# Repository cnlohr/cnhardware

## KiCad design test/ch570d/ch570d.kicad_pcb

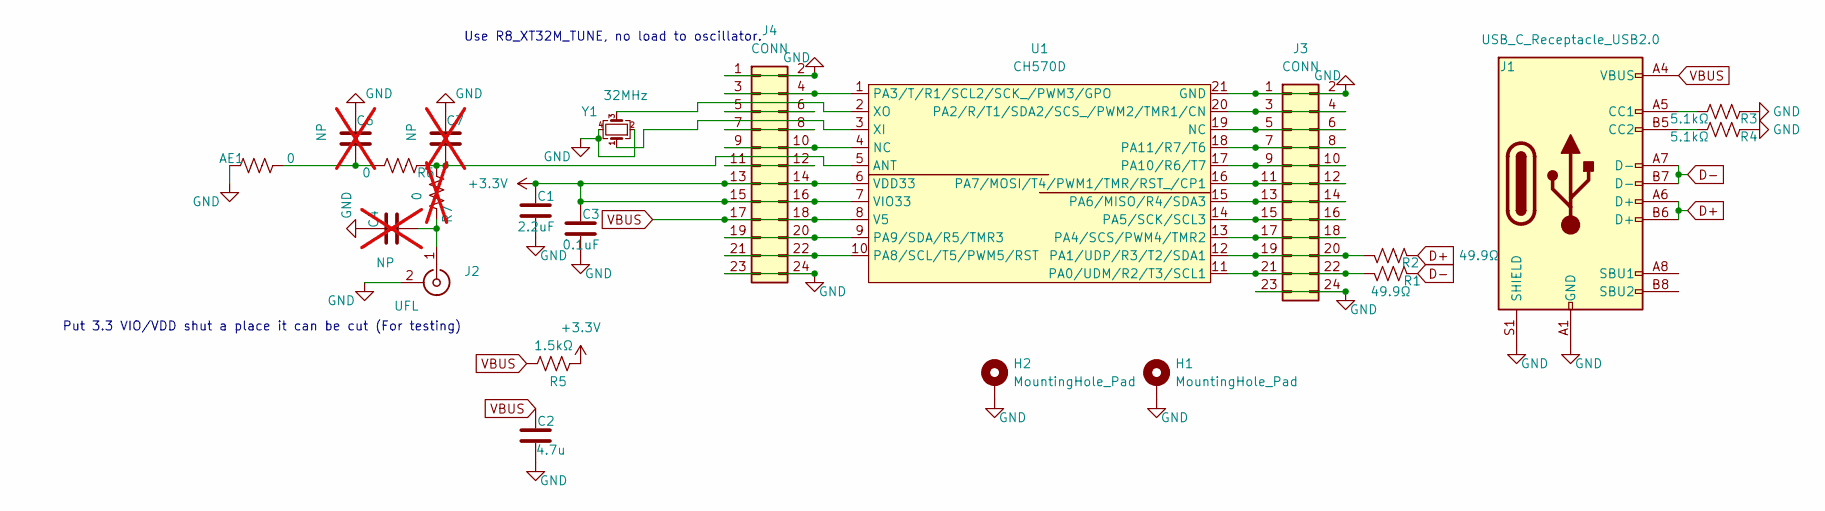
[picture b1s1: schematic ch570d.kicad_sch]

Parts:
AE1: 0; Texas_SWRA117D_2.4GHz_Right
C1: 2.2uF; C_0402_1005Metric; LCSC C12530
C2: 4.7u; C_0402_1005Metric; LCSC C23733
C3: 0.1uF; C_0402_1005Metric; LCSC C307331
C4, C6, C7: NP; C_0402_1005Metric; not fitted
H1, H2: MountingHole_Pad; MountingHole_2.2mm_M2_DIN965_Pad
J1: USB_C_Receptacle_USB2.0; USB_C_Receptacle_HRO_TYPE-C-31-M-12; LCSC C2765186
J2: UFL; U.FL_Molex_MCRF_73412-0110_Vertical; LCSC C496552
J3, J4: CONN; PinHeader_2x12_P2.54mm_Vertical; LCSC C5383110
R1, R2: 49.9Ω; R_0402_1005Metric; LCSC C25120
R3, R4: 5.1kΩ; R_0402_1005Metric; LCSC C25905
R5: 1.5kΩ; R_0402_1005Metric; LCSC C25867
R6: 0; R_0402_1005Metric; LCSC C17168
R7: 0; R_0402_1005Metric; LCSC C17168; not fitted
U1: CH570D; QFN-20-1EP_3x3mm_P0.4mm_EP1.65x1.65mm
Y1: 32MHz; Crystal_SMD_2016-4Pin_2.0x1.6mm; LCSC C2965582

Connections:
+3.3V: C1.1, C3.1, J4.13, J4.14, J4.15, J4.16, R5.2, U1.6 (VDD33), U1.7 (VIO33)
D+: J1.A6 (D+), J1.B6 (D+), R2.2
D-: J1.A7 (D-), J1.B7 (D-), R1.2
GND: AE1.2, C1.2, C2.2, C3.2, C4.1, C6.1, C7.1, H1.1, H2.1, J1.A1 (GND), J1.A12 (GND), J1.B1 (GND), J1.B12 (GND), J1.S1 (SHIELD), J2.2 (Ext), J3.1, J3.2, J3.23, J3.24, J4.1, J4.2, J4.23, J4.24, R3.2, R4.2, U1.21 (GND), Y1.2, Y1.4
unnamed: AE1.1, C6.2, R6.1
unnamed: J1.A5 (CC1), R3.1
unnamed: J1.B5 (CC2), R4.1
unnamed: C4.2, J2.1 (In), R7.1
unnamed: J3.3, J3.4, U1.20 (PA2/R/T1/SDA2/SCS_/PWM2/TMR1/CN)
unnamed: J3.5, J3.6, U1.19 (NC)
unnamed: J3.7, J3.8, U1.18 (PA11/R7/T6)
unnamed: J3.9, J3.10, U1.17 (PA10/R6/T7)
unnamed: J3.11, J3.12, U1.16 (PA7/MOSI/T4/PWM1/TMR/RST_/CP1)
unnamed: J3.13, J3.14, U1.15 (PA6/MISO/R4/SDA3)
unnamed: J3.15, J3.16, U1.14 (PA5/SCK/SCL3)
unnamed: J3.17, J3.18, U1.13 (PA4/SCS/PWM4/TMR2)
unnamed: J3.19, J3.20, R2.1, U1.12 (PA1/UDP/R3/T2/SDA1)
unnamed: J3.21, J3.22, R1.1, U1.11 (PA0/UDM/R2/T3/SCL1)
unnamed: J4.3, J4.4, U1.1 (PA3/T/R1/SCL2/SCK_/PWM3/GPO)
unnamed: J4.5, J4.6
unnamed: J4.7, J4.8
unnamed: J4.9, J4.10, U1.4 (NC)
unnamed: J4.11, J4.12
unnamed: J4.19, J4.20, U1.9 (PA9/SDA/R5/TMR3)
unnamed: J4.21, J4.22, U1.10 (PA8/SCL/T5/PWM5/RST)
unnamed: C7.2, R6.2, R7.2, U1.5 (ANT)
unnamed: U1.3 (XI), Y1.1
unnamed: U1.2 (XO), Y1.3
VBUS: C2.1, J1.A4 (VBUS), J1.A9 (VBUS), J1.B4 (VBUS), J1.B9 (VBUS), J4.17, J4.18, R5.1, U1.8 (V5)

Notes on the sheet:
Use R8_XT32M_TUNE, no load to oscillator.
Put 3.3 VIO/VDD shut a place it can be cut (For testing)

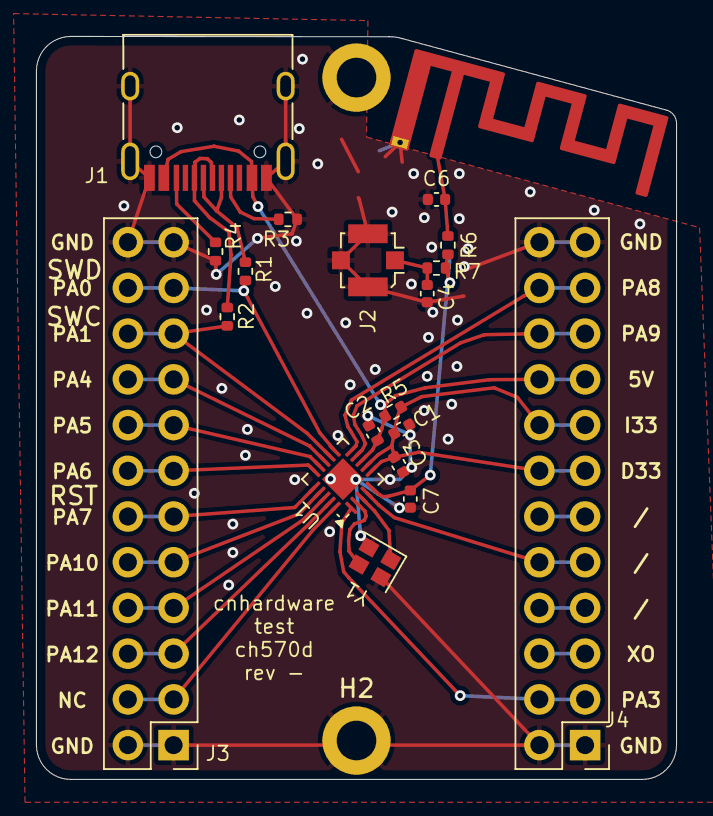
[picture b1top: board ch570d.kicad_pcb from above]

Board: 2 copper layers, 35.6 x 41.3 mm, 22 parts (0 on the bottom side), 29 nets.

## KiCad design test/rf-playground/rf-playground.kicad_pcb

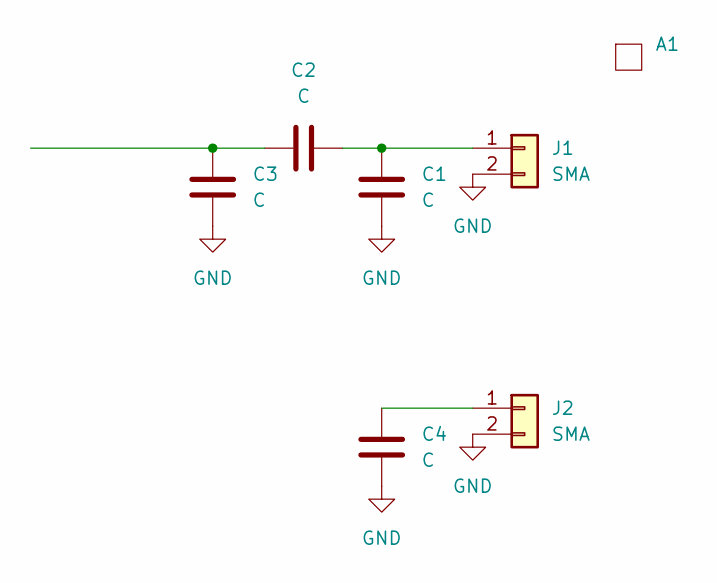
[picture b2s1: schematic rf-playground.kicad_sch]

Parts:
A1: maskgrid
C1, C2, C3, C4: C; C_0603_1608Metric
J1, J2: SMA; SMA_Amphenol_132289_EdgeMount

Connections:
GND: C1.2, C3.2, C4.2, J1.2, J2.2
unnamed: C2.1, C3.1
unnamed: C1.1, C2.2, J1.1
unnamed: C4.1, J2.1

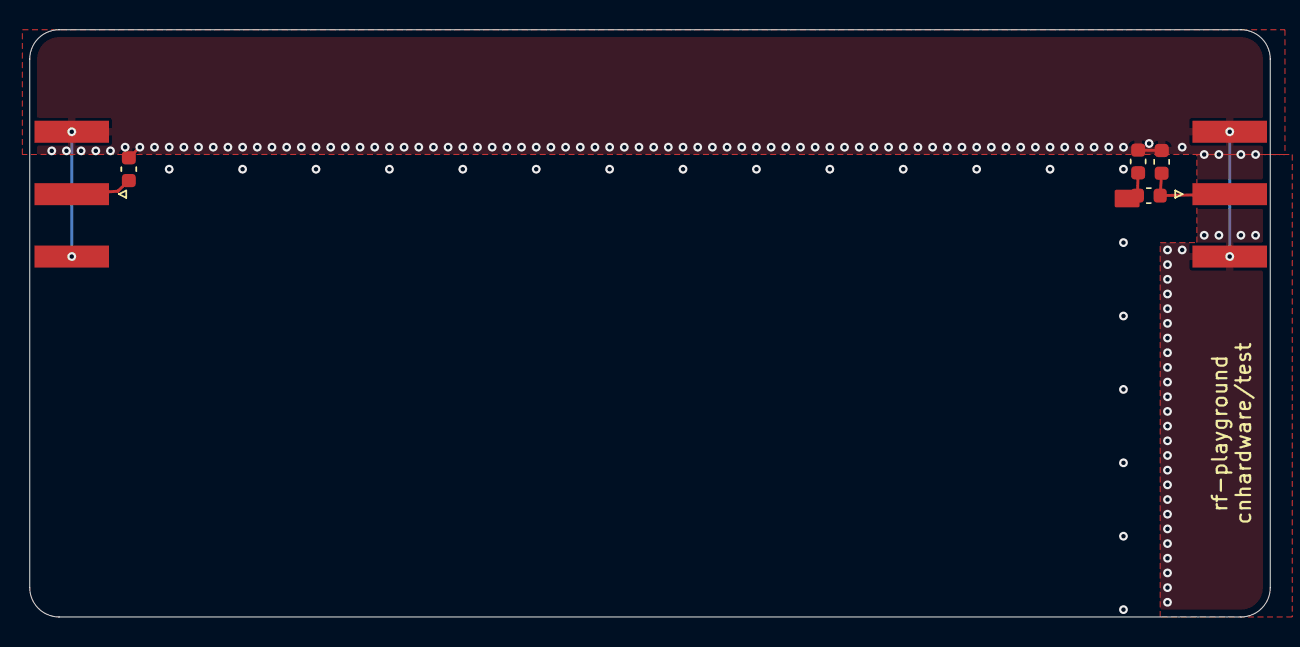
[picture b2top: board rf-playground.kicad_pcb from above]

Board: 2 copper layers, 84.5 x 40.0 mm, 8 parts (1 on the bottom side), 4 nets.

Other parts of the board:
A1#2: maskgrid

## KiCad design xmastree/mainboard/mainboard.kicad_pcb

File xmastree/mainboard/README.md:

Moved here: https://github.com/cnlohr/x32-ws2812-usbhs-breakout

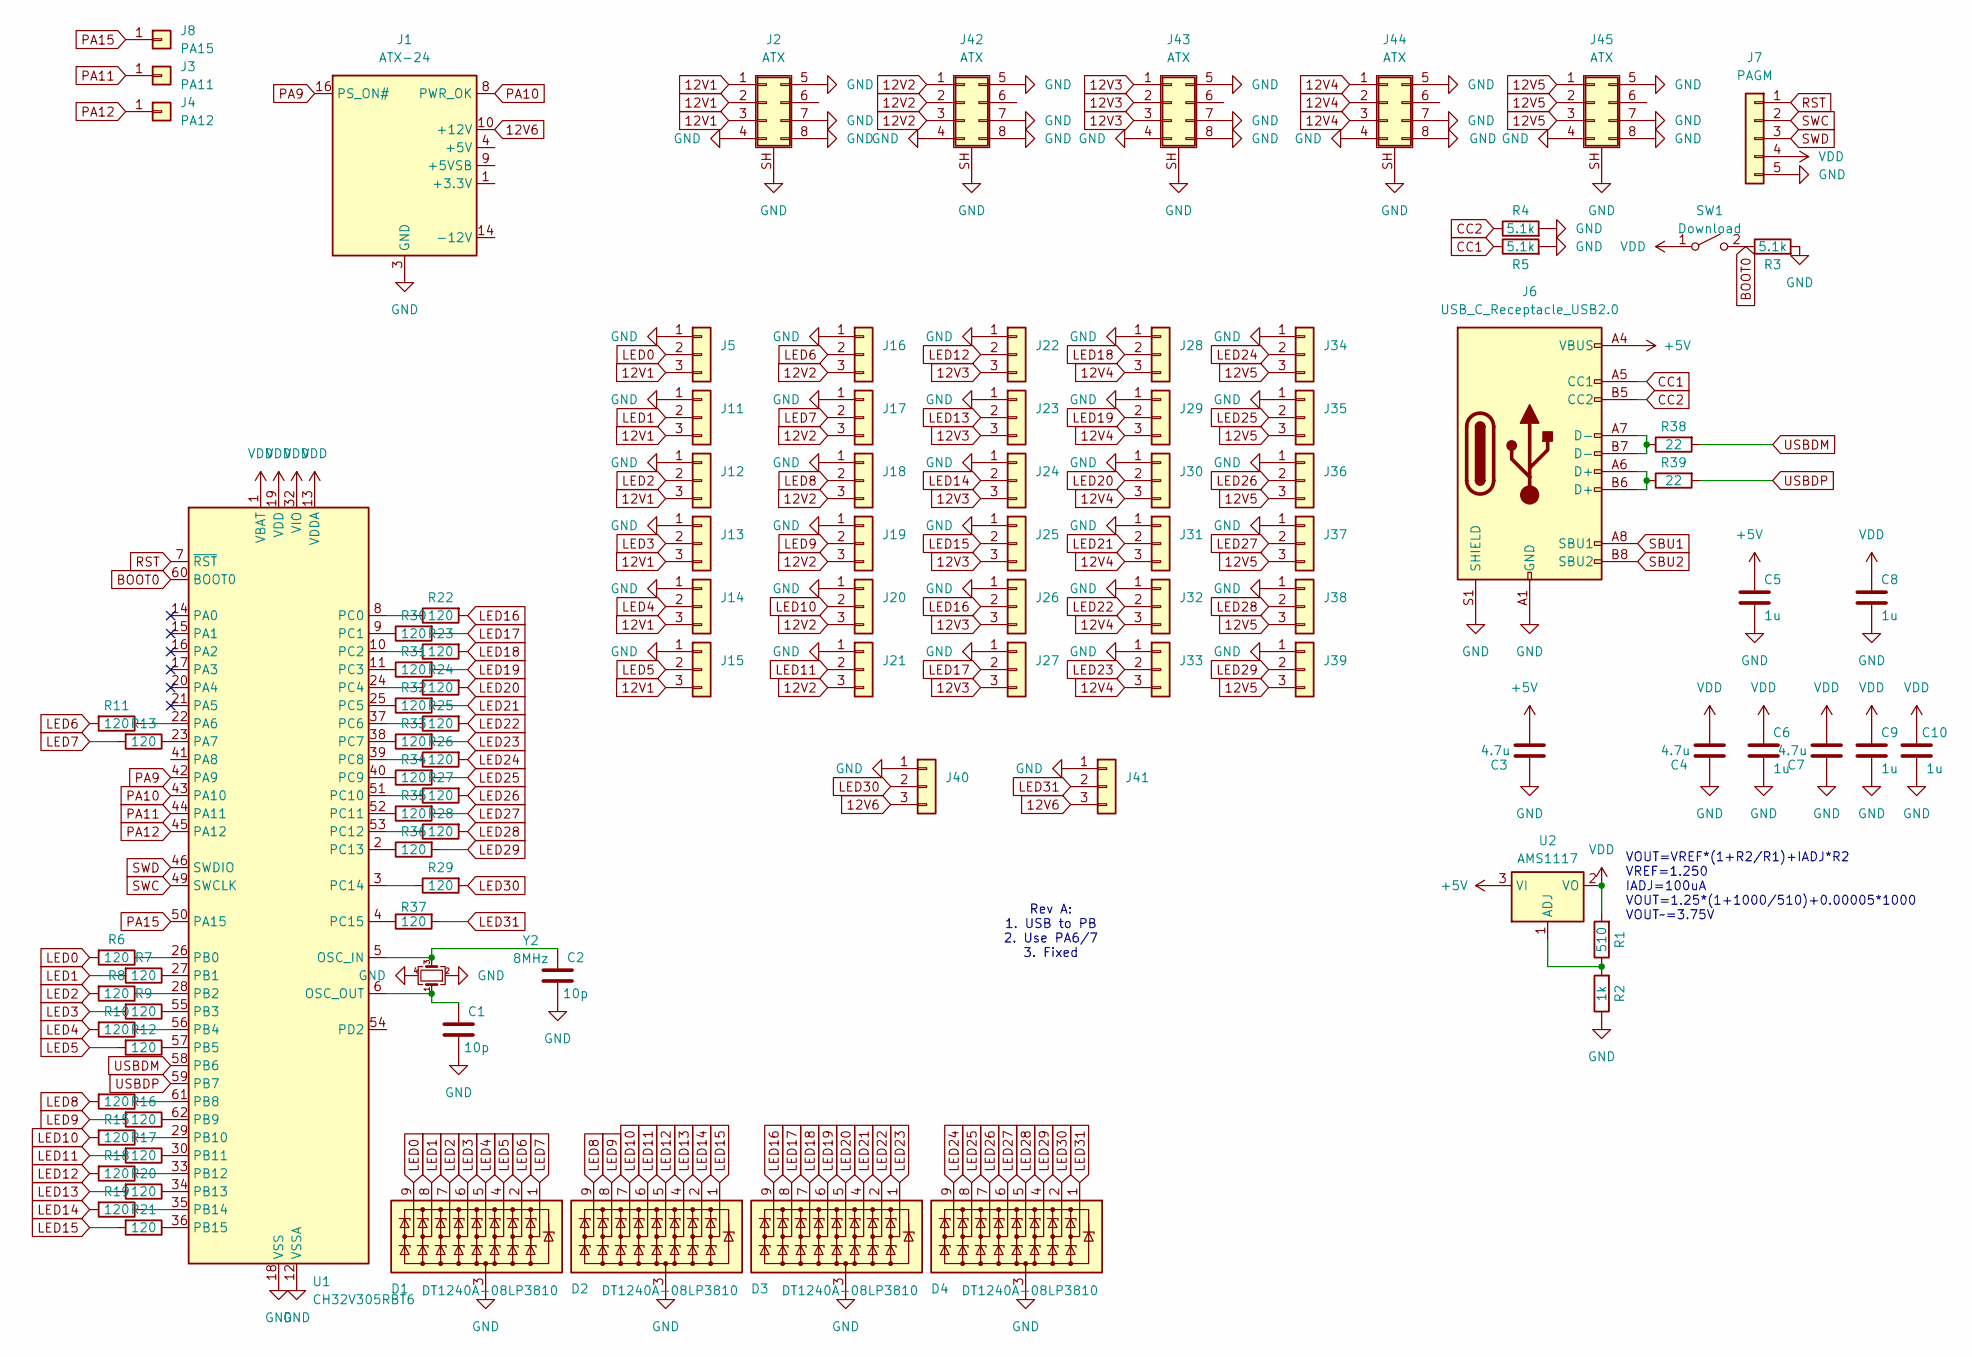
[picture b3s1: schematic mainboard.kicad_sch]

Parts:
C1, C2: 10p; R_0402_1005Metric; LCSC C32949
C3, C4, C7: 4.7u; C_0805_2012Metric; LCSC C1779
C5, C6, C8, C9, C10: 1u; R_0402_1005Metric; LCSC C52923
D1, D2, D3, D4: DT1240A-08LP3810; UDFN-9_1.0x3.8mm_P0.5mm; LCSC C526598
J1: ATX-24; Molex_Mini-Fit_Jr_5566-24A2_2x12_P4.20mm_Vertical; LCSC C114125
J2, J42, J43, J44, J45: ATX; Molex_Mini-Fit_-PCI_EXPRESS-_2x04_P4.20mm_Vertical; LCSC C2886679
J3: PA11; TestPoint_Pad_D1.0mm
J4: PA12; TestPoint_Pad_D1.0mm
J5, J11, J12, J13, J14, J15, J16, J17, J18, J19, J20, J21, J22, J23, J24, J25, J26, J27, J28, J29, J30, J31, J32, J33, J34, J35, J36, J37, J38, J39, J40, J41: LED; TerminalBlock_TE_282834-3_1x03_P2.54mm_Horizontal; LCSC C234181
J6: USB_C_Receptacle_USB2.0; USB_C_Receptacle_HRO_TYPE-C-31-M-12; LCSC C2765186
J7: PAGM; PinHeader_1x05_P2.54mm_Vertical; LCSC C32713271
J8: PA15; TestPoint_Pad_D1.0mm
R1: 510; R_0402_1005Metric; LCSC C25123
R2: 1k; R_0402_1005Metric; LCSC C11702
R3, R4, R5: 5.1k; R_0402_1005Metric; LCSC C25905
R6, R7, R8, R9, R10, R11, R12, R13, R14, R15, R16, R17, R18, R19, R20, R21, R22, R23, R24, R25, R26, R27, R28, R29, R30, R31, R32, R33, R34, R35, R36, R37: 120; R_0402_1005Metric; LCSC C25079
R38, R39: 22; R_0402_1005Metric; LCSC C25092
SW1: Download; SW_SPST_TL3342; LCSC C318884
U1: CH32V305RBT6; LQFP-64_10x10mm_P0.5mm; LCSC C5187529
U2: AMS1117; SOT-223-3_TabPin2; LCSC C110475
Y2: 8MHz; Crystal_SMD_3225-4Pin_3.2x2.5mm_HandSoldering; LCSC C367183

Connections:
12V1: J2.1, J2.2, J2.3, J5.3, J11.3, J12.3, J13.3, J14.3, J15.3
12V2: J16.3, J17.3, J18.3, J19.3, J20.3, J21.3, J42.1, J42.2, J42.3
12V3: J22.3, J23.3, J24.3, J25.3, J26.3, J27.3, J43.1, J43.2, J43.3
12V4: J28.3, J29.3, J30.3, J31.3, J32.3, J33.3, J44.1, J44.2, J44.3
12V5: J34.3, J35.3, J36.3, J37.3, J38.3, J39.3, J45.1, J45.2, J45.3
12V6: J1.10 (+12V), J1.11 (+12V), J40.3, J41.3
+5V: C3.2, C5.2, J6.A4 (VBUS), J6.A9 (VBUS), J6.B4 (VBUS), J6.B9 (VBUS), U2.3 (VI)
BOOT0: R3.1, SW1.2 (B), U1.60 (BOOT0)
CC1: J6.A5 (CC1), R5.1
CC2: J6.B5 (CC2), R4.1
GND: C1.1, C2.1, C3.1, C4.1, C5.1, C6.1, C7.1, C8.1, C9.1, C10.1, D1.3 (A), D2.3 (A), D3.3 (A), D4.3 (A), J1.3 (GND), J1.5 (GND), J1.7 (GND), J1.15 (GND), J1.17 (GND), J1.18 (GND), J1.19 (GND), J1.24 (GND), J2.4, J2.5, J2.7, J2.8, J2.SH (Shield), J5.1, J6.A1 (GND), J6.A12 (GND), J6.B1 (GND), J6.B12 (GND), J6.S1 (SHIELD), J7.5, J11.1, J12.1, J13.1, J14.1, J15.1, J16.1, J17.1, J18.1, J19.1, J20.1, J21.1, J22.1, J23.1, J24.1, J25.1, J26.1, J27.1, J28.1, J29.1, J30.1, J31.1, J32.1, J33.1, J34.1, J35.1, J36.1, J37.1, J38.1, J39.1, J40.1, J41.1, J42.4, J42.5, J42.7, J42.8, J42.SH (Shield), J43.4, J43.5, J43.7, J43.8, J43.SH (Shield), J44.4, J44.5, J44.7, J44.8, J44.SH (Shield), J45.4, J45.5, J45.8, J45.SH (Shield), R2.1, R3.2, R4.2, R5.2, U1.12 (VSSA), U1.18 (VSS), U1.31 (VSS), U1.47 (VSS), U1.63 (VSS), Y2.2, Y2.4
LED0: D1.9 (K8), J5.2, R6.2
LED1: D1.8 (K7), J11.2, R7.2
LED2: D1.7 (K6), J12.2, R8.2
LED3: D1.6 (K5), J13.2, R9.2
LED4: D1.5 (K4), J14.2, R10.2
LED5: D1.4 (K3), J15.2, R12.2
LED6: D1.2 (K2), J16.2, R11.2
LED7: D1.1 (K1), J17.2, R13.2
LED8: D2.9 (K8), J18.2, R14.2
LED9: D2.8 (K7), J19.2, R16.2
LED10: D2.7 (K6), J20.2, R15.2
LED11: D2.6 (K5), J21.2, R17.2
LED12: D2.5 (K4), J22.2, R18.2
LED13: D2.4 (K3), J23.2, R20.2
LED14: D2.2 (K2), J24.2, R19.2
LED15: D2.1 (K1), J25.2, R21.2
LED16: D3.9 (K8), J26.2, R22.2
LED17: D3.8 (K7), J27.2, R30.2
LED18: D3.7 (K6), J28.2, R23.2
LED19: D3.6 (K5), J29.2, R31.2
LED20: D3.5 (K4), J30.2, R24.2
LED21: D3.4 (K3), J31.2, R32.2
LED22: D3.2 (K2), J32.2, R25.2
LED23: D3.1 (K1), J33.2, R33.2
LED24: D4.9 (K8), J34.2, R26.2
LED25: D4.8 (K7), J35.2, R34.2
LED26: D4.7 (K6), J36.2, R27.2
LED27: D4.6 (K5), J37.2, R35.2
LED28: D4.5 (K4), J38.2, R28.2
LED29: D4.4 (K3), J39.2, R36.2
LED30: D4.2 (K2), J40.2, R29.2
LED31: D4.1 (K1), J41.2, R37.2
unnamed: J1.1 (+3.3V), J1.2 (+3.3V), J1.12 (+3.3V), J1.13 (+3.3V)
unnamed: J1.4 (+5V), J1.6 (+5V), J1.21 (+5V), J1.22 (+5V), J1.23 (+5V)
unnamed: J6.A6 (D+), J6.B6 (D+), R39.1
unnamed: J6.A7 (D-), J6.B7 (D-), R38.1
unnamed: C2.2, U1.5 (OSC_IN), Y2.3
unnamed: C1.2, U1.6 (OSC_OUT), Y2.1
unnamed: R11.1, U1.22 (PA6)
unnamed: R13.1, U1.23 (PA7)
unnamed: R6.1, U1.26 (PB0)
unnamed: R7.1, U1.27 (PB1)
unnamed: R8.1, U1.28 (PB2)
unnamed: R9.1, U1.55 (PB3)
unnamed: R10.1, U1.56 (PB4)
unnamed: R12.1, U1.57 (PB5)
unnamed: R14.1, U1.61 (PB8)
unnamed: R16.1, U1.62 (PB9)
unnamed: R15.1, U1.29 (PB10)
unnamed: R17.1, U1.30 (PB11)
unnamed: R18.1, U1.33 (PB12)
unnamed: R20.1, U1.34 (PB13)
unnamed: R19.1, U1.35 (PB14)
unnamed: R21.1, U1.36 (PB15)
unnamed: R22.1, U1.8 (PC0)
unnamed: R30.1, U1.9 (PC1)
unnamed: R23.1, U1.10 (PC2)
unnamed: R31.1, U1.11 (PC3)
unnamed: R24.1, U1.24 (PC4)
unnamed: R32.1, U1.25 (PC5)
unnamed: R25.1, U1.37 (PC6)
unnamed: R33.1, U1.38 (PC7)
unnamed: R26.1, U1.39 (PC8)
unnamed: R34.1, U1.40 (PC9)
unnamed: R27.1, U1.51 (PC10)
unnamed: R35.1, U1.52 (PC11)
unnamed: R28.1, U1.53 (PC12)
unnamed: R36.1, U1.2 (PC13)
unnamed: R29.1, U1.3 (PC14)
unnamed: R37.1, U1.4 (PC15)
unnamed: R1.1, R2.2, U2.1 (ADJ)
PA9: J1.16 (PS_ON#), U1.42 (PA9)
PA10: J1.8 (PWR_OK), U1.43 (PA10)
PA11: J3.1, U1.44 (PA11)
PA12: J4.1, U1.45 (PA12)
PA15: J8.1, U1.50 (PA15)
RST: J7.1, U1.7 (~RST)
SBU1: J6.A8 (SBU1)
SBU2: J6.B8 (SBU2)
SWC: J7.2, U1.49 (SWCLK)
SWD: J7.3, U1.46 (SWDIO)
USBDM: R38.2, U1.58 (PB6)
USBDP: R39.2, U1.59 (PB7)
VDD: C4.2, C6.2, C7.2, C8.2, C9.2, C10.2, J7.4, R1.2, SW1.1 (A), U1.1 (VBAT), U1.13 (VDDA), U1.19 (VDD), U1.32 (VIO), U1.48 (VDD), U1.64 (VIO), U2.2 (VO)

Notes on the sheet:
Rev A: 1. USB to PB 2. Use PA6/7 3. Fixed
VOUT=VREF*(1+R2/R1)+IADJ*R2 VREF=1.250 IADJ=100uA VOUT=1.25*(1+1000/510)+0.00005*1000 VOUT~=3.75V

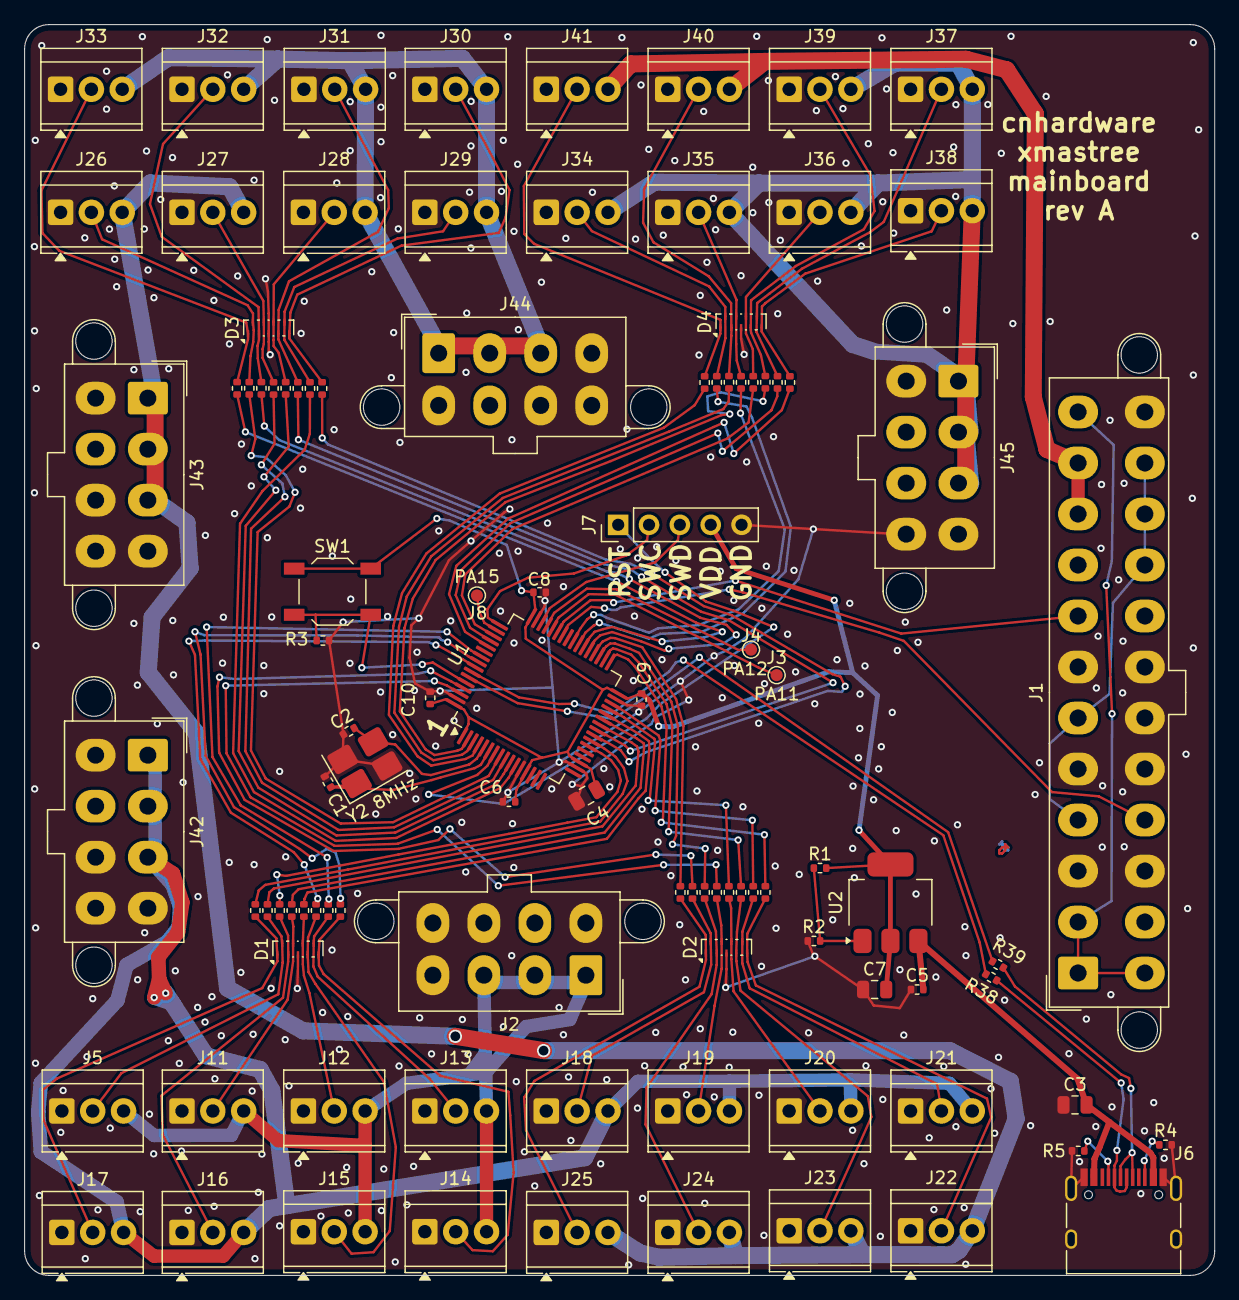
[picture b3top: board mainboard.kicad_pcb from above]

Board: 2 copper layers, 98.0 x 103.0 mm, 100 parts (0 on the bottom side), 93 nets.

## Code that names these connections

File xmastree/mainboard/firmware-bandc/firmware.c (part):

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	volatile uint16_t set_one[1]  __attribute__((aligned(4))) =  { 0xffff };


	funPinMode( PA3, GPIO_CFGLR_OUT_10Mhz_PP ); // Old PSU on signal
	funPinMode( PA9, GPIO_CFGLR_OUT_10Mhz_PP ); // New PSU on signal

    Delay_Ms(200);
	// Enable DMA
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	RCC->APB2PCENR = RCC_APB2Periph_TIM1 | RCC_APB2Periph_TIM10 | RCC_APB2Periph_AFIO  | RCC_APB2Periph_GPIOA | RCC_APB2Periph_GPIOB | RCC_APB2Periph_GPIOC | RCC_APB2Periph_GPIOD | RCC_APB2Periph_GPIOE;
	RCC->APB1PCENR |= RCC_APB1Periph_TIM2;

	funPinMode( PA9, GPIO_CFGLR_OUT_50Mhz_PP );
	funDigitalWrite( PA9, 0);

	funPinMode( PA6, GPIO_CFGLR_OUT_10Mhz_PP );
	funPinMode( PA7, GPIO_CFGLR_OUT_10Mhz_PP );

	GPIOC->CFGLR = 0x11111111; // All output.  All 10MHz
	GPIOC->CFGHR = 0x11111111; // All output.  All 10MHz

	GPIOB->CFGLR = 0x11111111; // All output.  All 10MHz
	GPIOB->CFGHR = 0xbb111111; // All output.  All 10MHz  (Except for USB pins, PB6, PB7)

	set_one[0] = 0xffff;

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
